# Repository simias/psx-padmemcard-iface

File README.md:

# ATmega4809-based interface for PlayStation Memory Cards and Controllers

This repository contains the schematics and controller code to create a simple
UART-based interface to PlayStation Memory Card and Controllers.

The design uses a simple ATmega4809 microcontroller running at 4MHz.

The PlayStation Pad/MemCard connector uses both 3.5V (for all communication
signals) and 7.5V (mainly used for DualShock rumble motors and other
power-hungry features). I think that most devices will work perfectly fine with
only the 3.5V input, but in order to be as close as possible to the real
hardware I power my board with a 7.5V that I can wire to the relevant pin of the
Pad/MemCard port, and I use a cheap off-the-shelf DC-DC module to convert that
7.5V to 3.5V which I use to power the controller.

I also send the 5V from the UART-to-USB and UPDI inputs to the DC-DC input
(through diodes) to allow powering the board from USB, but in this case this
same 5V will be sent to the Pad/MemCards instead of a true 7.5V.

A single LED is pulsed with PWM to show activity.

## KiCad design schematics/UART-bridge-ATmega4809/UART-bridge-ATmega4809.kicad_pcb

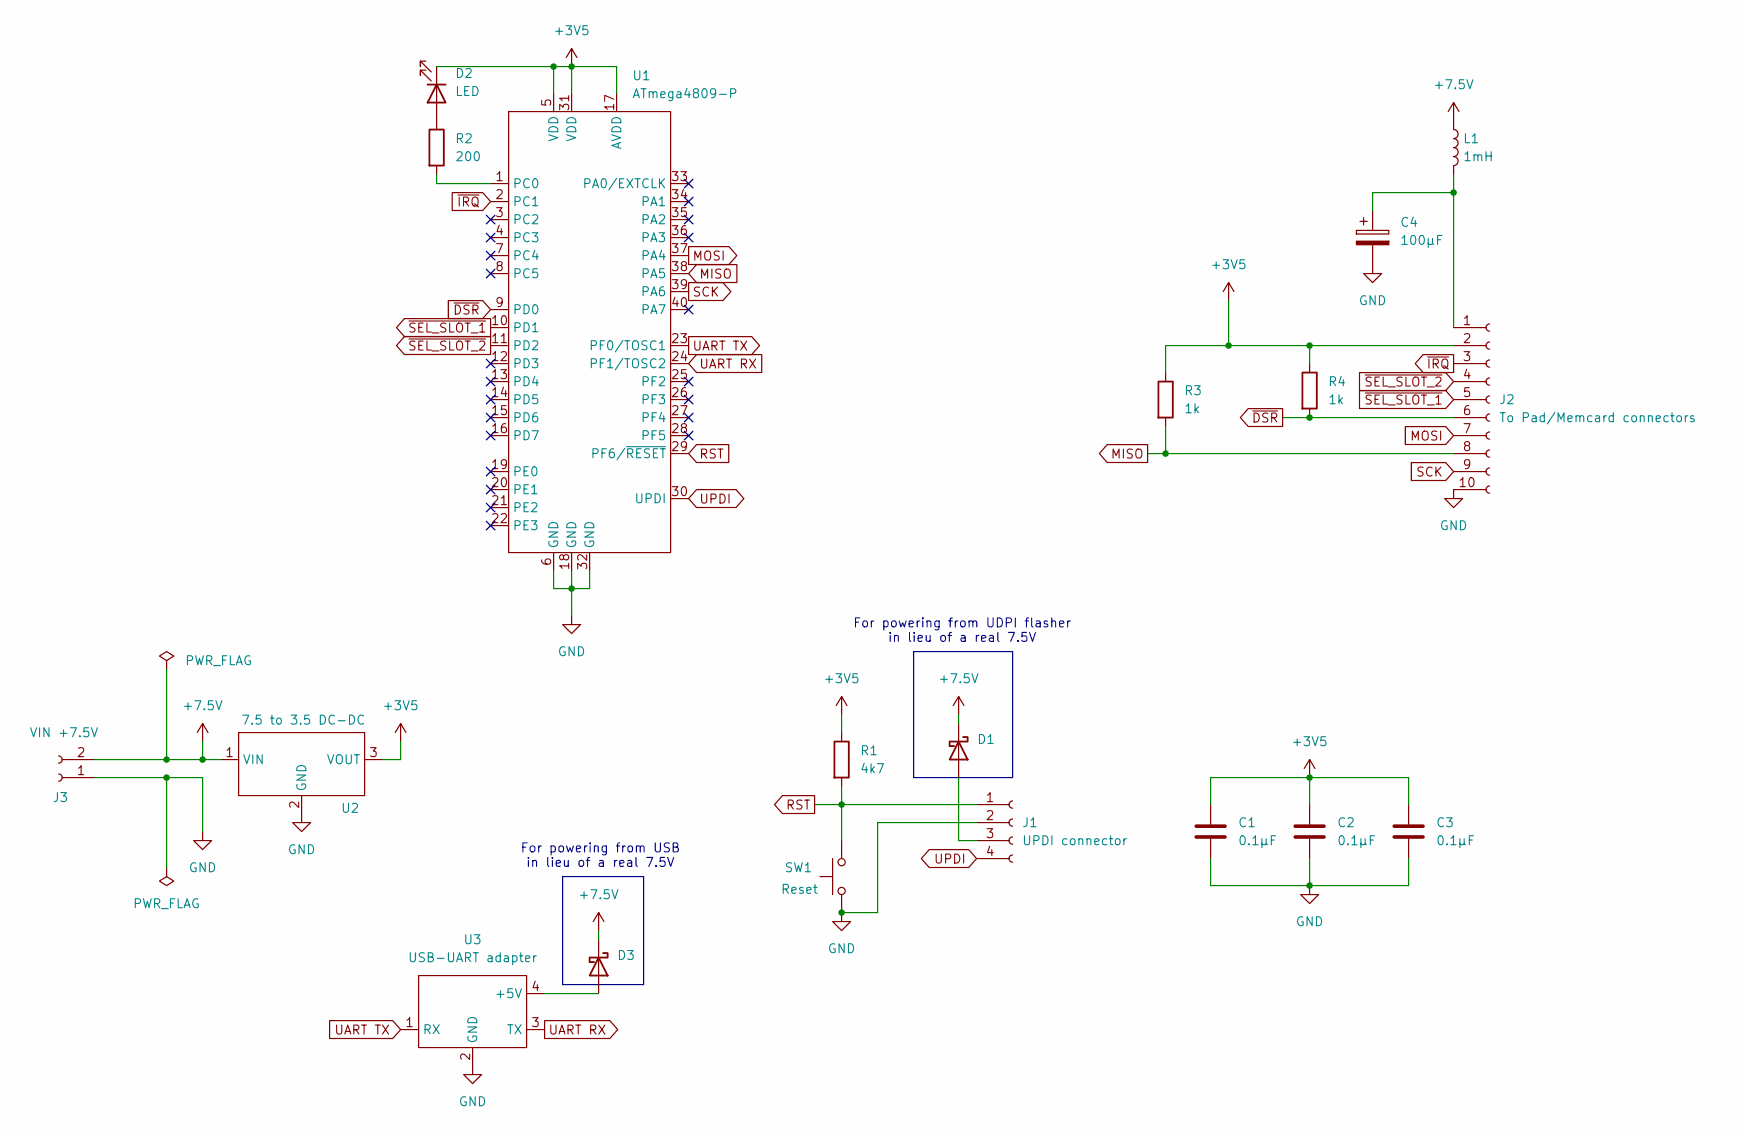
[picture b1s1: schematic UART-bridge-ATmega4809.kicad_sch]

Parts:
C1, C2, C3: 0.1µF; C_Disc_D5.0mm_W2.5mm_P5.00mm
C4: 100µF; C_Radial_D5.0mm_H11.0mm_P2.00mm
D1, D3: D_Schottky; D_A-405_P7.62mm_Horizontal
D2: LED; LED_D5.0mm_Clear
J1: UPDI connector; PinSocket_1x04_P2.54mm_Vertical
J2: To Pad/Memcard connectors; PinSocket_1x10_P2.54mm_Vertical
J3: VIN +7.5V; PinSocket_1x02_P2.54mm_Vertical
L1: 1mH; L_Radial_D7.0mm_P3.00mm
R1: 4k7; R_Axial_DIN0207_L6.3mm_D2.5mm_P7.62mm_Horizontal
R2: 200; R_Axial_DIN0207_L6.3mm_D2.5mm_P7.62mm_Horizontal
R3, R4: 1k; R_Axial_DIN0207_L6.3mm_D2.5mm_P7.62mm_Horizontal
SW1: Reset; SW_PUSH_6mm
U1: ATmega4809-P; DIP-40_W15.24mm_Socket
U2: 7.5 to 3.5 DC-DC; PinSocket_1x03_P2.54mm_Vertical
U3: USB-UART adapter; PinSocket_1x06_P2.54mm_Vertical

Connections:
+3V5: C1.1, C2.1, C3.1, D2.1 (K), J2.2, R1.1, R3.1, R4.1, U1.5 (VDD), U1.17 (AVDD), U1.31 (VDD), U2.3 (VOUT)
+7.5V: D1.1 (K), D3.1 (K), J3.2, L1.1, U2.1 (VIN)
GND: C1.2, C2.2, C3.2, C4.2, J1.2, J2.10, J3.1, SW1.1, U1.6 (GND), U1.18 (GND), U1.32 (GND), U2.2 (GND), U3.2 (GND)
MISO: J2.8, R3.2, U1.38 (PA5)
MOSI: J2.7, U1.37 (PA4)
unnamed: D1.2 (A), J1.3
unnamed: D2.2 (A), R2.1
unnamed: D3.2 (A), U3.4 (+5V)
unnamed: C4.1, J2.1, L1.2
unnamed: R2.2, U1.1 (PC0)
RST: J1.1, R1.2, SW1.2, U1.29 (PF6/~RESET)
SCK: J2.9, U1.39 (PA6)
UART RX: U1.24 (PF1/TOSC2), U3.3 (TX)
UART TX: U1.23 (PF0/TOSC1), U3.1 (RX)
UPDI: J1.4, U1.30 (UPDI)
~DSR: J2.6, R4.2, U1.9 (PD0)
~IRQ: J2.3, U1.2 (PC1)
~SEL_SLOT_1: J2.5, U1.10 (PD1)
~SEL_SLOT_2: J2.4, U1.11 (PD2)

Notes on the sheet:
For powering from USB in lieu of a real 7.5V
For powering from UDPI flasher in lieu of a real 7.5V

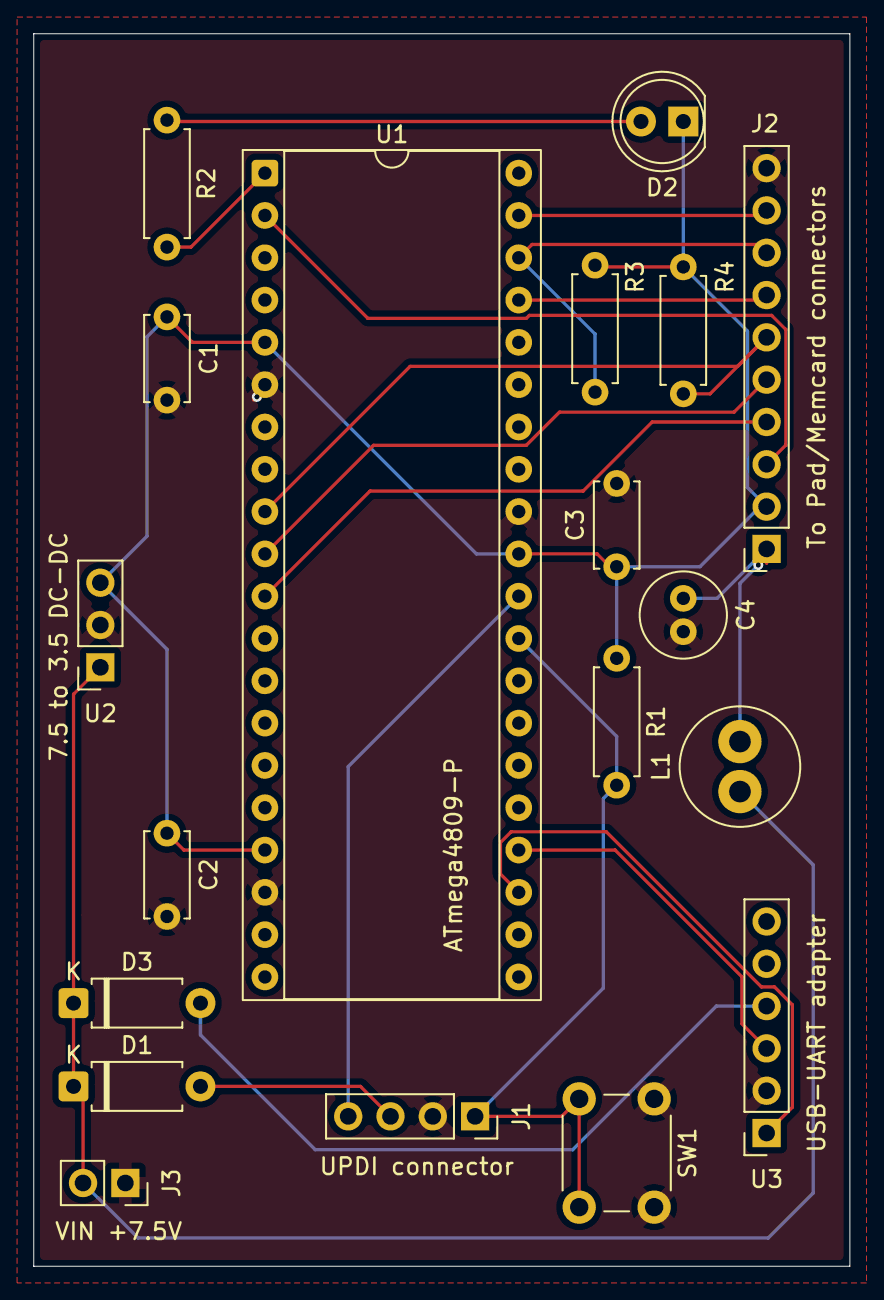
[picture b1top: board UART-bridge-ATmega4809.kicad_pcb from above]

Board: 2 copper layers, 49.0 x 74.0 mm, 19 parts (0 on the bottom side), 19 nets.

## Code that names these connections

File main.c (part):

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
static void pwm_init(void)
{
    /* LED on PC0: use PWM */
    PORTC.DIR |= PIN0_bm;

    PORTMUX.TCAROUTEA &= ~PORTMUX_TCA0_gm;
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
    rtc_init();

    /* /DSR: PD0, IRQ on falling edge, (warning: needs external 1kohm pull-up,
     * in my tests this internal PU is not sufficient) */
    PORTD.PIN0CTRL = PORT_ISC_FALLING_gc;

    /* /SEL1: PD1, /SEL2: PD2 */
    PORTD.DIR |= PIN1_bm | PIN2_bm;
    PORTD.OUTSET |= PIN1_bm | PIN2_bm;

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
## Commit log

2026-06-13 UART OK
2026-06-14 Added PWM code
2026-06-15 Use CMP0BUF instead of CMP0 for PWM updates to avoid glitches
2026-06-15 Implement SPI interface
2026-06-15 Add RTC + IRQ support
2026-06-16 Compile with avr-gcc 15
2026-06-16 Communication with GamePad OK
2026-06-16 Added schematics and README.md
2026-06-16 Added UART RX handling
2026-06-17 Implement idle mode
2026-06-17 Tweak schematics, add IRQ pin for future-proofing
2026-06-17 Design PCB prototype
2026-06-18 Implement padmem.py, controller probe OK
2026-06-19 Implement device listing
2026-06-19 Bugfix, MC dump OK
2026-06-19 Improve `exchange` command formatting
2026-06-19 Improve various timeouts
2026-06-19 Change framing format
2026-06-20 Make UART TX async
2026-06-20 Make command exchange asynchronous
2026-06-20 Code cleanup
2026-06-20 Add missing newline in mcdump
2026-06-20 PocketStation memory dump OK
2026-06-20 Move slot selection to the top command
2026-06-20 Implement PocketStation RTC read
2026-06-20 Implement PocketStation RTC sync
2026-06-21 Fix bogus rtcsync
2026-06-21 Implement pks-showdisplay
2026-06-21 Implement RLE encoding to speed up UART commands
2026-06-21 Send NACK on CSUM errors
2026-06-21 Implement mcrestore
2026-06-23 Allow printing with IRQ disabled
2026-06-23 Implement pks-memwrite
